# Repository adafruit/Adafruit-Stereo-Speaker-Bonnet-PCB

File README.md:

## Adafruit Stereo Speaker Bonnet PCB

<a href="http://www.adafruit.com/products/3346"><br/>
Click here to purchase one from the Adafruit shop</a>

PCB files for the Adafruit Stereo Speaker Bonnet for Raspberry Pi. Format is EagleCAD schematic and board layout
* http://www.adafruit.com/product/3346

### Description

Hey Mr. DJ! Turn up that Raspberry Pi mix to the max with this cute 3W Stereo Amplifier Bonnet for Raspberry Pi. (It's not big enough to be an official HAT, so we called it a bonnet, you see?) It's the exact same size as a Raspberry Pi Zero but works with any and all Raspberry Pi computers with a 2x20 connector - A+, B+, Zero, Pi 2, Pi 3, etc. We've tested it out with Raspbian (the official operating system) and RetroPie.

This Bonnet uses I2S a digital sound standard, so you get really crisp audio. The digital data goes right into the amplifier so there's no static like you hear from the headphone jack. And it's super easy to get started. Just plug in any 4Ω to 8Ω speakers, up to 3 Watts, run our installer script on any Raspberry Pi, reboot and you're ready to jam!

Each order comes as a fully tested and assembled PCB and 2x extra terminal blocks. No soldering required if you're using our 3 Watt speaker set, just plug and play.

### Updates

#### 2021-11-29 swap left and right channels 

Swap channels on PCB. This impacts only the speakers connected via JST-PH header X3 when replacing the board. The revision is now called "B+". Component coordinates and paste stencil of Rev B can be re-used.

\- HW

#### 2021-11-29 implement shutdown option to fix pop issue

Problem: MAX98357A used here needs to be disabled when no clocks are present to avoid pops during boot.

Fix: Project files have been updated to include an option to connect !SD_MODE inputs to GPIO4. See [current schematic](assets/Adafruit%20Speaker%20Bonnet.sch.pdf).

Modification instructions for previous PCB revision: Below is a description how to modify the older PCB version to implement the fix. R1 (394) needs to be replaced with 220k soldered to one pad only as shown in the crop. the LEFT channel pin 4 trace going to the capacitors needs to be cut near the capacitors. Subsequently, part of the remaining trace is exposed and tinned to form a new pad.  GPIO4, the new pad, as well as the unconnected pad of the 220k resistor need to be connected using thin (<= 0.3 mm) enamel wire or equivalent.

\- HW

### License

Adafruit invests time and resources providing this open source design, please support Adafruit and open-source hardware by purchasing products from [Adafruit](https://www.adafruit.com)!

Designed by Limor Fried/Ladyada for Adafruit Industries.

Creative Commons Attribution/Share-Alike, all text above must be included in any redistribution. See license.txt for additional details.

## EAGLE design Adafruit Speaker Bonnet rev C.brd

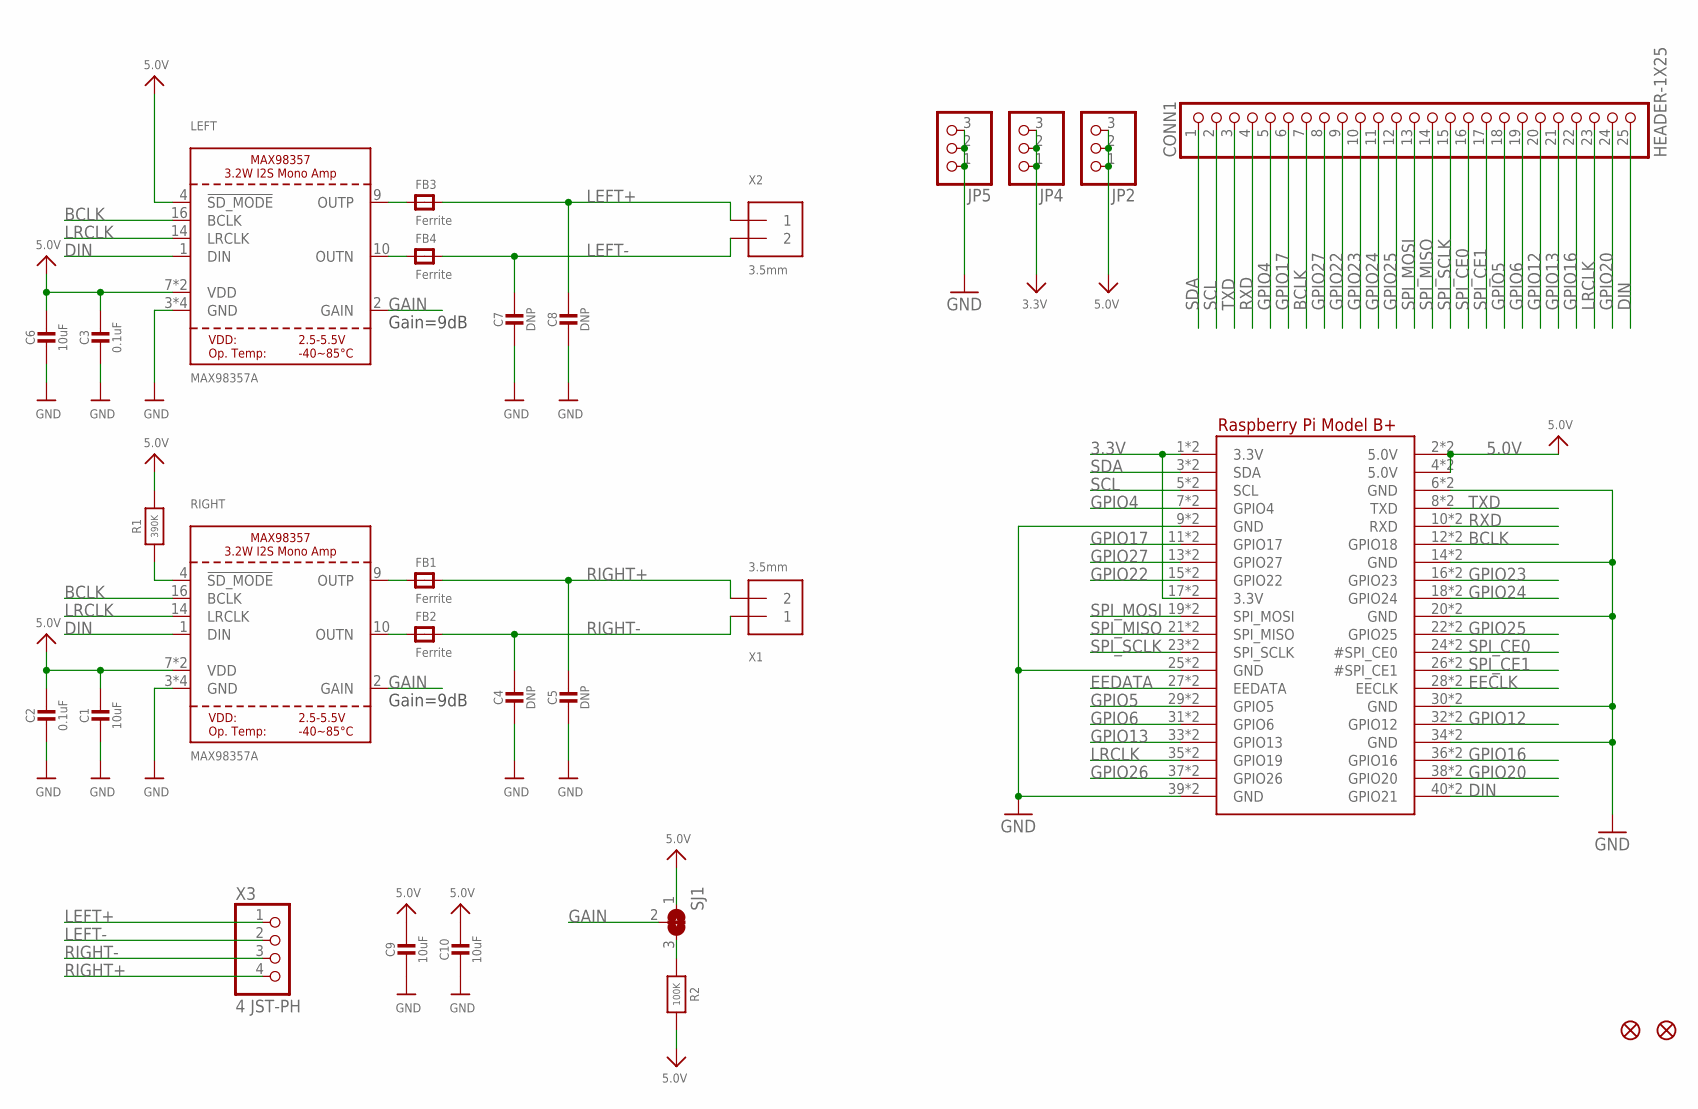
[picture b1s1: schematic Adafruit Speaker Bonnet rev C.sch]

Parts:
C1, C6, C9, C10: 10uF; 0805-NO
C2, C3: 0.1uF; 0805-NO
C4, C5, C7, C8: DNP; 0805-NO
CONN1: HEADER-1X25; 1X25_ROUND_70MIL
FB1, FB2, FB3, FB4: Ferrite; 0805-NO
FID1, FID2: FIDUCIAL_1MM
JP2, JP4, JP5: HEADER-1X376MIL; 1X03_ROUND_76
LEFT: MAX98357A; QFN16_3MM
R1: 390K; 0805-NO
R2: 100K; 0805-NO
RIGHT: MAX98357A; QFN16_3MM
RPI1: RASPBERRYPI_BPLUS_BONNET_THMSMT; PI_BONNET_THMSMT
SJ1: SOLDERJUMPER_2WAY; SOLDERJUMPER_2WAY_OPEN_NOPASTE
X1, X2: 3.5mm; TERMBLOCK_1X2-3.5MM
X3: 4 JST-PH; JSTPH4

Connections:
3.3V: JP4.1, JP4.2, JP4.3, RPI1.1 (3.3V), RPI1.17 (3.3V), RPI1.S1 (3.3V), RPI1.S17 (3.3V)
5.0V: C1.1, C2.1, C3.1, C6.1, C9.1, C10.1, JP2.1, JP2.2, JP2.3, LEFT.4 (!SD_MODE), LEFT.7 (VDD), LEFT.8 (VDD), R1.2, R2.2, RIGHT.7 (VDD), RIGHT.8 (VDD), RPI1.2 (5.0V), RPI1.4 (5.0V), RPI1.S2 (5.0V), RPI1.S4 (5.0V), SJ1.1
BCLK: CONN1.7, LEFT.16 (BCLK), RIGHT.16 (BCLK), RPI1.12 (GPIO18), RPI1.S12 (GPIO18)
DIN: CONN1.25, LEFT.1 (DIN), RIGHT.1 (DIN), RPI1.40 (GPIO21), RPI1.S40 (GPIO21)
EECLK: RPI1.28 (EECLK), RPI1.S28 (EECLK)
EEDATA: RPI1.27 (EEDATA), RPI1.S27 (EEDATA)
GAIN: LEFT.2 (GAIN), RIGHT.2 (GAIN), SJ1.2
GND: C1.2, C2.2, C3.2, C4.2, C5.2, C6.2, C7.2, C8.2, C9.2, C10.2, JP5.1, JP5.2, JP5.3, LEFT.3 (GND), LEFT.11 (GND), LEFT.15 (GND), LEFT.THERMAL (GND), RIGHT.3 (GND), RIGHT.11 (GND), RIGHT.15 (GND), RIGHT.THERMAL (GND), RPI1.6 (GND), RPI1.9 (GND), RPI1.14 (GND), RPI1.20 (GND), RPI1.25 (GND), RPI1.30 (GND), RPI1.34 (GND), RPI1.39 (GND), RPI1.S6 (GND), RPI1.S9 (GND), RPI1.S14 (GND), RPI1.S20 (GND), RPI1.S25 (GND), RPI1.S30 (GND), RPI1.S34 (GND), RPI1.S39 (GND)
GPIO4: CONN1.5, RPI1.7 (GPIO4), RPI1.S7 (GPIO4)
GPIO5: CONN1.18, RPI1.29 (GPIO5), RPI1.S29 (GPIO5)
GPIO6: CONN1.19, RPI1.31 (GPIO6), RPI1.S31 (GPIO6)
GPIO12: CONN1.20, RPI1.32 (GPIO12), RPI1.S32 (GPIO12)
GPIO13: CONN1.21, RPI1.33 (GPIO13), RPI1.S33 (GPIO13)
GPIO16: CONN1.22, RPI1.36 (GPIO16), RPI1.S36 (GPIO16)
GPIO17: CONN1.6, RPI1.11 (GPIO17), RPI1.S11 (GPIO17)
GPIO20: CONN1.24, RPI1.38 (GPIO20), RPI1.S38 (GPIO20)
GPIO22: CONN1.9, RPI1.15 (GPIO22), RPI1.S15 (GPIO22)
GPIO23: CONN1.10, RPI1.16 (GPIO23), RPI1.S16 (GPIO23)
GPIO24: CONN1.11, RPI1.18 (GPIO24), RPI1.S18 (GPIO24)
GPIO25: CONN1.12, RPI1.22 (GPIO25), RPI1.S22 (GPIO25)
GPIO26: RPI1.37 (GPIO26), RPI1.S37 (GPIO26)
GPIO27: CONN1.8, RPI1.13 (GPIO27), RPI1.S13 (GPIO27)
LEFT+: C8.1, FB3.2, X2.1, X3.1
LEFT-: C7.1, FB4.2, X2.2, X3.2
LRCLK: CONN1.23, LEFT.14 (LRCLK), RIGHT.14 (LRCLK), RPI1.35 (GPIO19), RPI1.S35 (GPIO19)
unnamed: FB4.1, LEFT.10 (OUTN)
unnamed: FB3.1, LEFT.9 (OUTP)
unnamed: FB2.1, RIGHT.10 (OUTN)
unnamed: FB1.1, RIGHT.9 (OUTP)
unnamed: R2.1, SJ1.3
RIGHT+: C5.1, FB1.2, X1.2, X3.4
RIGHT-: C4.1, FB2.2, X1.1, X3.3
RXD: CONN1.4, RPI1.10 (RXD), RPI1.S10 (RXD)
SCL: CONN1.2, RPI1.5 (SCL), RPI1.S5 (SCL)
SDA: CONN1.1, RPI1.3 (SDA), RPI1.S3 (SDA)
SD_MODE: R1.1, RIGHT.4 (!SD_MODE)
SPI_CE0: CONN1.16, RPI1.24 (#SPI_CE0), RPI1.S24 (#SPI_CE0)
SPI_CE1: CONN1.17, RPI1.26 (#SPI_CE1), RPI1.S26 (#SPI_CE1)
SPI_MISO: CONN1.14, RPI1.21 (SPI_MISO), RPI1.S21 (SPI_MISO)
SPI_MOSI: CONN1.13, RPI1.19 (SPI_MOSI), RPI1.S19 (SPI_MOSI)
SPI_SCLK: CONN1.15, RPI1.23 (SPI_SCLK), RPI1.S23 (SPI_SCLK)
TXD: CONN1.3, RPI1.8 (TXD), RPI1.S8 (TXD)

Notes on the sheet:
Gain=9dB

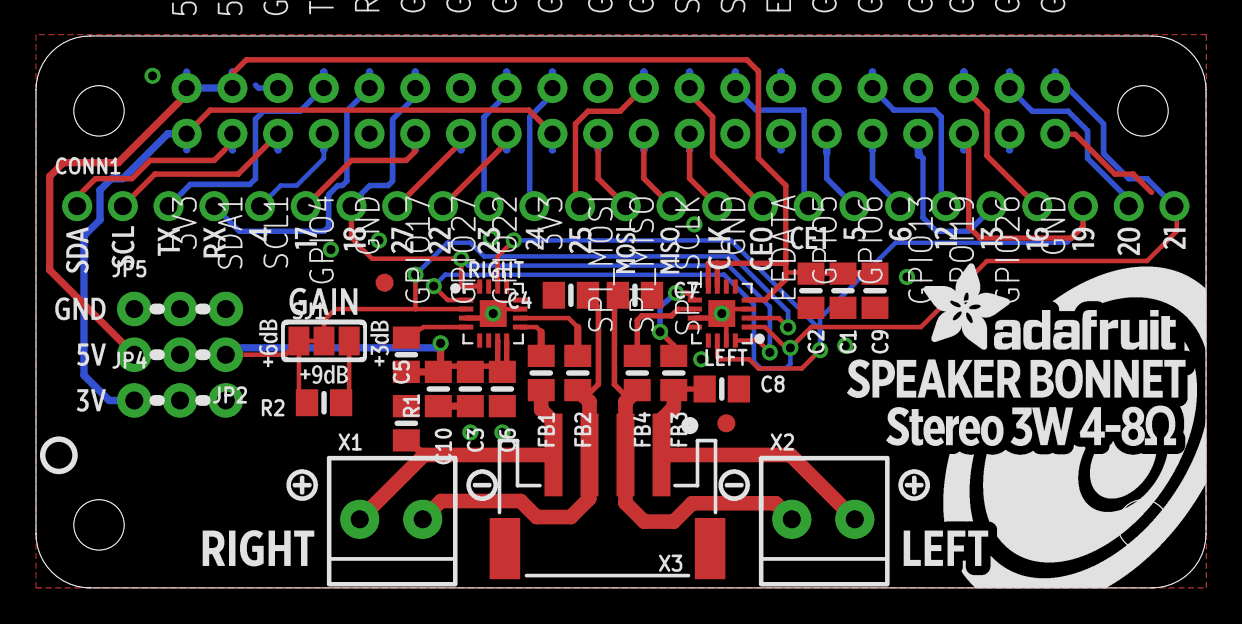
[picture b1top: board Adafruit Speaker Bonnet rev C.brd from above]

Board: 2 copper layers, 65.0 x 30.7 mm, 31 parts (0 on the bottom side), 42 nets.

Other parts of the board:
U$11: PCBFEAT-REV-040
U$30: BONNET_SPEAKER_REVB

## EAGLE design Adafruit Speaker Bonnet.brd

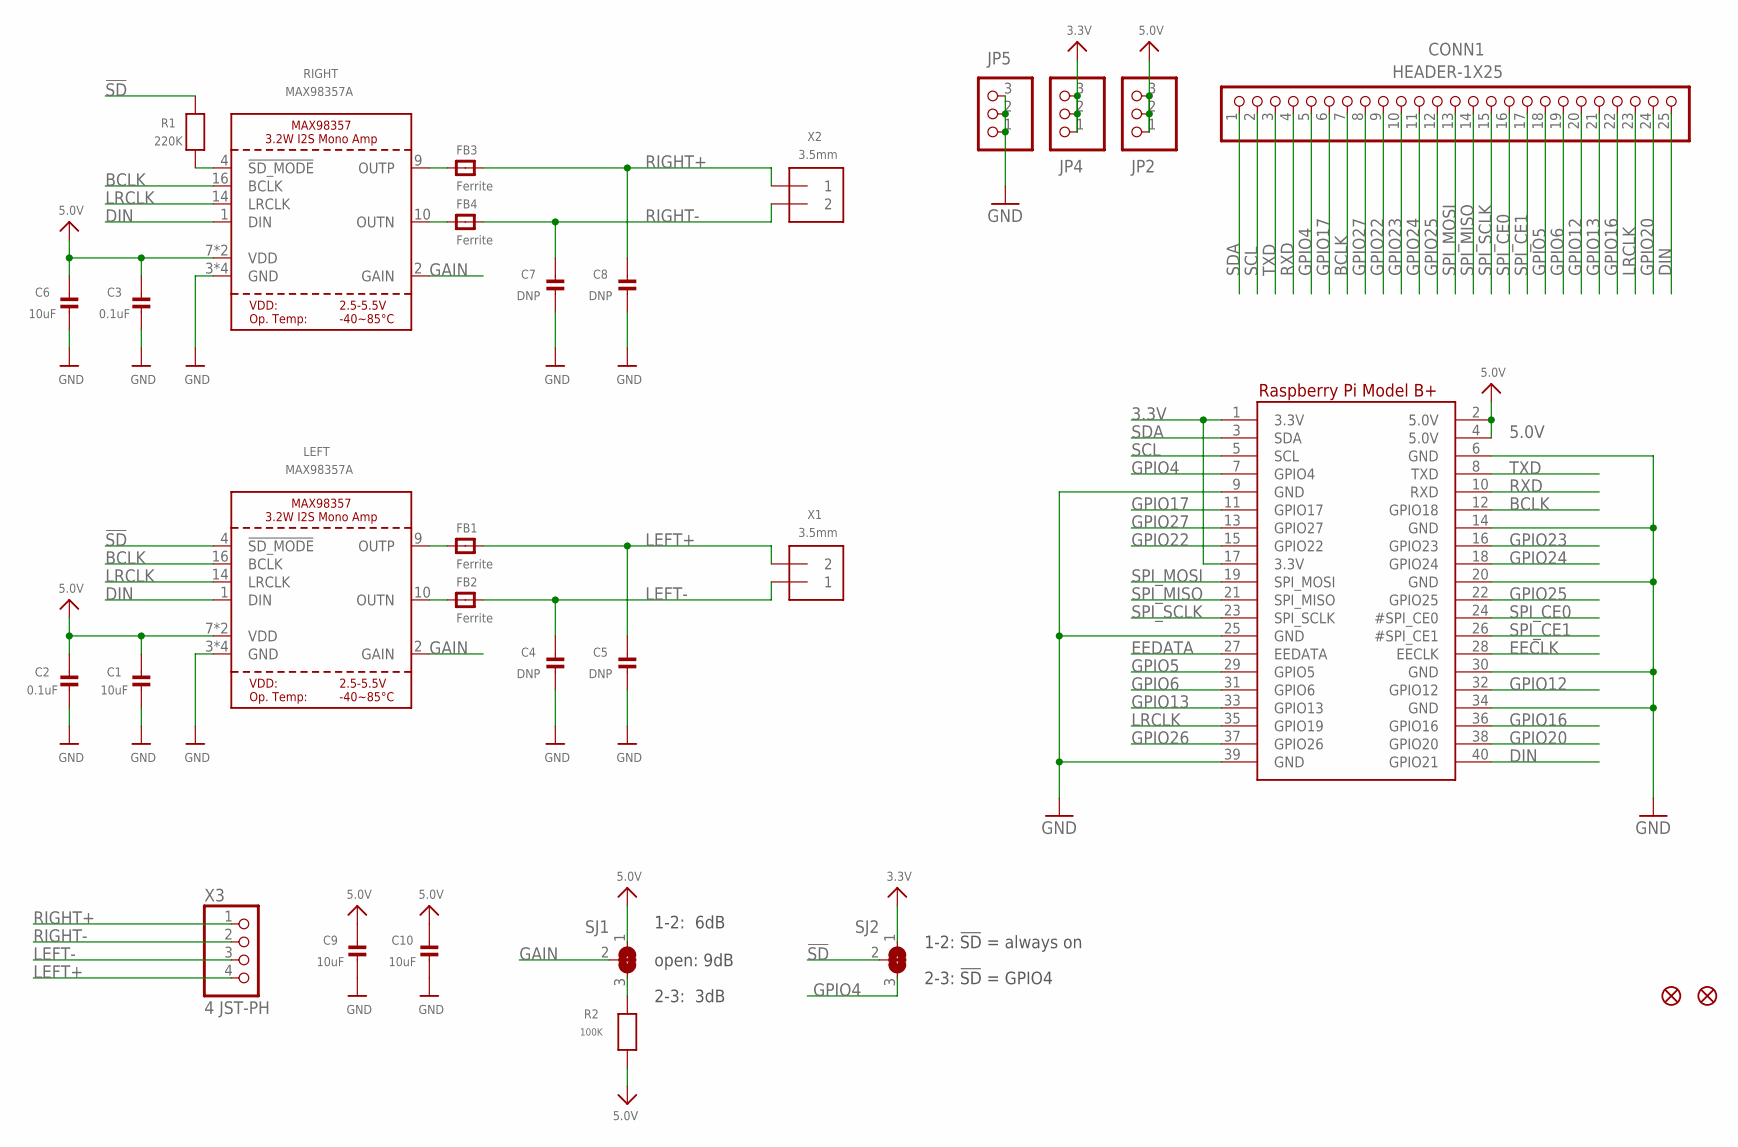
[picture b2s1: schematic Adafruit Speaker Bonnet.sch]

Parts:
C1, C6, C9, C10: 10uF; 0805-NO
C2, C3: 0.1uF; 0805-NO
C4, C5, C7, C8: DNP; 0805-NO
CONN1: HEADER-1X25; 1X25_ROUND_70MIL
FB1, FB2, FB3, FB4: Ferrite; 0805-NO
FID1, FID2: FIDUCIAL""; FIDUCIAL_1MM
JP2, JP4, JP5: HEADER-1X376MIL; 1X03_ROUND_76
LEFT: MAX98357A; QFN16_3MM
R1: 220K; 0805-NO
R2: 100K; 0805-NO
RIGHT: MAX98357A; QFN16_3MM
RPI1: RASPBERRYPI_BPLUS_BONNETNODIM; PI_BONNET_NODIM
SJ1, SJ2: SOLDERJUMPER_2WAY; SOLDERJUMPER_2WAY_OPEN_NOPASTE
X1, X2: 3.5mm; TERMBLOCK_1X2-3.5MM
X3: 4 JST-PH; JSTPH4

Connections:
3.3V: JP4.1, JP4.2, JP4.3, RPI1.1 (3.3V), RPI1.17 (3.3V), SJ2.1
5.0V: C1.1, C2.1, C3.1, C6.1, C9.1, C10.1, JP2.1, JP2.2, JP2.3, LEFT.7 (VDD), LEFT.8 (VDD), R2.2, RIGHT.7 (VDD), RIGHT.8 (VDD), RPI1.2 (5.0V), RPI1.4 (5.0V), SJ1.1
!SD: LEFT.4 (!SD_MODE), R1.1, SJ2.2
BCLK: CONN1.7, LEFT.16 (BCLK), RIGHT.16 (BCLK), RPI1.12 (GPIO18)
DIN: CONN1.25, LEFT.1 (DIN), RIGHT.1 (DIN), RPI1.40 (GPIO21)
EECLK: RPI1.28 (EECLK)
EEDATA: RPI1.27 (EEDATA)
GAIN: LEFT.2 (GAIN), RIGHT.2 (GAIN), SJ1.2
GND: C1.2, C2.2, C3.2, C4.2, C5.2, C6.2, C7.2, C8.2, C9.2, C10.2, JP5.1, JP5.2, JP5.3, LEFT.3 (GND), LEFT.11 (GND), LEFT.15 (GND), LEFT.THERMAL (GND), RIGHT.3 (GND), RIGHT.11 (GND), RIGHT.15 (GND), RIGHT.THERMAL (GND), RPI1.6 (GND), RPI1.9 (GND), RPI1.14 (GND), RPI1.20 (GND), RPI1.25 (GND), RPI1.30 (GND), RPI1.34 (GND), RPI1.39 (GND)
GPIO4: CONN1.5, RPI1.7 (GPIO4), SJ2.3
GPIO5: CONN1.18, RPI1.29 (GPIO5)
GPIO6: CONN1.19, RPI1.31 (GPIO6)
GPIO12: CONN1.20, RPI1.32 (GPIO12)
GPIO13: CONN1.21, RPI1.33 (GPIO13)
GPIO16: CONN1.22, RPI1.36 (GPIO16)
GPIO17: CONN1.6, RPI1.11 (GPIO17)
GPIO20: CONN1.24, RPI1.38 (GPIO20)
GPIO22: CONN1.9, RPI1.15 (GPIO22)
GPIO23: CONN1.10, RPI1.16 (GPIO23)
GPIO24: CONN1.11, RPI1.18 (GPIO24)
GPIO25: CONN1.12, RPI1.22 (GPIO25)
GPIO26: RPI1.37 (GPIO26)
GPIO27: CONN1.8, RPI1.13 (GPIO27)
LEFT+: C5.1, FB1.2, X1.2, X3.4
LEFT-: C4.1, FB2.2, X1.1, X3.3
LRCLK: CONN1.23, LEFT.14 (LRCLK), RIGHT.14 (LRCLK), RPI1.35 (GPIO19)
unnamed: FB4.1, RIGHT.10 (OUTN)
unnamed: FB3.1, RIGHT.9 (OUTP)
unnamed: R1.2, RIGHT.4 (!SD_MODE)
unnamed: FB2.1, LEFT.10 (OUTN)
unnamed: FB1.1, LEFT.9 (OUTP)
unnamed: R2.1, SJ1.3
RIGHT+: C8.1, FB3.2, X2.1, X3.1
RIGHT-: C7.1, FB4.2, X2.2, X3.2
RXD: CONN1.4, RPI1.10 (RXD)
SCL: CONN1.2, RPI1.5 (SCL)
SDA: CONN1.1, RPI1.3 (SDA)
SPI_CE0: CONN1.16, RPI1.24 (#SPI_CE0)
SPI_CE1: CONN1.17, RPI1.26 (#SPI_CE1)
SPI_MISO: CONN1.14, RPI1.21 (SPI_MISO)
SPI_MOSI: CONN1.13, RPI1.19 (SPI_MOSI)
SPI_SCLK: CONN1.15, RPI1.23 (SPI_SCLK)
TXD: CONN1.3, RPI1.8 (TXD)

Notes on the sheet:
1-2: 6dB
2-3: 3dB
open: 9dB
1-2: !SD! = always on
2-3: !SD! = GPIO4

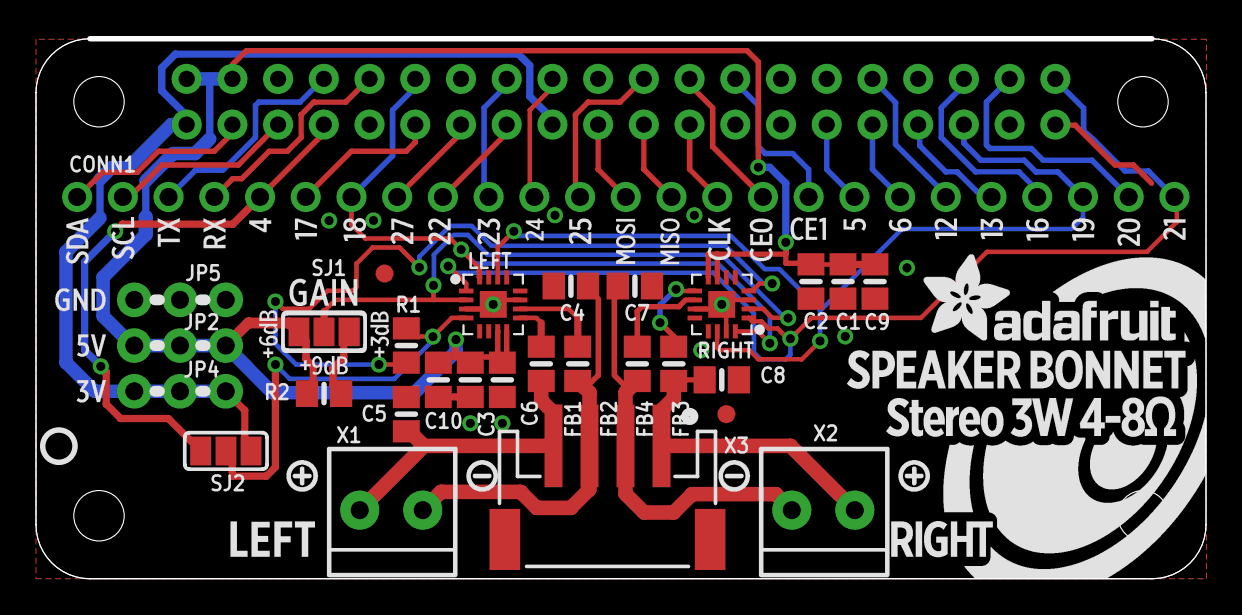
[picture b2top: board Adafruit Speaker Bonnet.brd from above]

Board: 2 copper layers, 64.7 x 29.8 mm, 32 parts (0 on the bottom side), 40 nets.

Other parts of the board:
U$11: PCBFEAT-REV-040
U$30: BONNET_SPEAKER_REVB_LR

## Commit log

2016-12-07 init
2021-11-29 fix pop problem
    MAX98357A not in shutdown when no clocks are present (no auto-detect). !SD_MODE is a multi-level comparator with an internal 100k pull-down.
    * disconnect !SD_MODE pins from PU to 5V
    * connect LEFT channel directly to selector
    * connect RIGHT channel through R_SMALL (3.3V:220k) to selector
    * selector allows selection between always-on (PU to 3.3V instead of 5V to avoid accidental GPIO bridging to 5V) and GPIO4
2021-11-29 fix clearance issue arount mounting hole, update readme
2021-11-29 reconnect missing signal
2021-11-29 fix part identifiers
2021-11-29 swap LEFT-RIGHT
    * swap channels (does not impact software side)
    * upate silkscreen (now right-side output is actually RIGHT channel)
2021-11-29 update readme
    recent changes preserve pick&place coordinates and orientations, BOM change is limited to R1 (390k -> 220k). The RevB stencil can be re-used.
2021-12-13 Add rev C.
2024-12-02 add rev D

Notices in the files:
parts and their libraries:
microbuilder: This work is placed in the public domain, and may be freely used for commercial and non-commercial work with the following conditions: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
